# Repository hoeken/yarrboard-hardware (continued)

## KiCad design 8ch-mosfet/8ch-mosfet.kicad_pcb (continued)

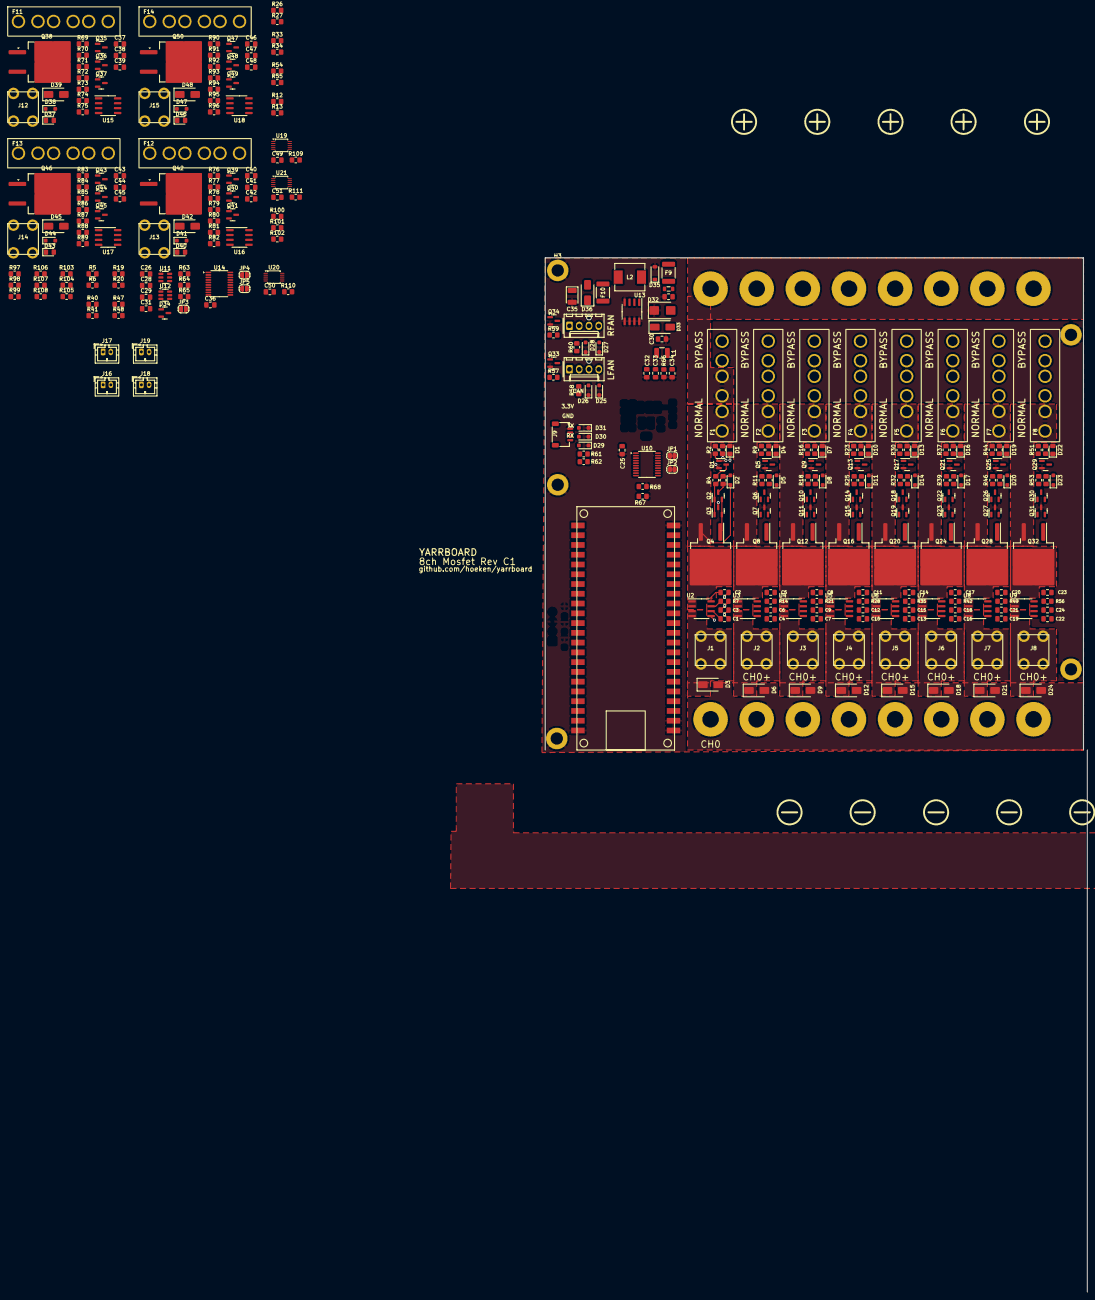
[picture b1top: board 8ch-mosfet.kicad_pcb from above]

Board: 4 copper layers, 329 parts (0 on the bottom side), 202 nets.

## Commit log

2023-11-18 removed non-hardware bits.
2023-11-19 removed old boards directory.
2023-12-13 added user holes for dxf export
2023-12-15 added user hole drawings for cad
2023-12-20 started looking at esp32-s3 based boards.
2024-08-14 changed to MCP3564
2024-08-15 changed to new s3 module
2024-08-15 more progress on new 8ch board.
2024-08-15 new design is going to be sick.
2024-08-15 updated the busbar
2024-08-15 updated busbar design.
2024-08-15 big update - 12ch, volt adc, senders, etc.
2024-08-16 component layout looking crispy.
2024-08-16 i think FrothFET is the winner!
2024-08-16 i think i figured out the tank sensors?
2024-08-16 more layout work. going to be a beast.
2024-08-16 renaming
2024-08-16 better name.
2024-08-16 moved 8ch mosfet / frothfet-12ch to own repo.
2024-08-16 removing old/obsolete boards.
2024-08-17 added a bunch of 3d models.
2024-08-18 updated fuse with 3d mode.
2024-10-06 updated models and footprints.
2025-08-11 missing some models.
2025-08-14 tmc2209 and esp32-s3-pico
2025-08-15 updates to the esp32-s3-pico
2025-09-12 added some 3d models.
2025-10-01 lots of library work for boards.
2025-10-06 library update
2025-10-06 models and footprints
2025-11-14 added buzzer and standoff for sendit rev c
2025-12-12 added a bunch of models/footprints/symbols
2026-04-18 old changes catchup.
2026-04-18 removed old document
